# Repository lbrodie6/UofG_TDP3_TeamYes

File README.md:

# UofG_TDP3_TeamYes
UofG TDP3 repo for KiCAD files and code
# File Structure
- hardware: KiCad files. All PCBs can be done within the Main_Project file
    - mechanical: Mechanical CAD files. Fusion 360 .f3d, STLs and Gcode files for 3D printing are all stored here
    - photomasks: Photomasks for PCB fabrication output
- lib: Footprint libraries. Contains any custom footprints used (such as for the FRDM board).
- software: Contains C++ code

## Reference
- TCS34725 Color Sensor design files: https://github.com/adafruit/Adafruit-Flora-TCS34725-Color-Sensor-PCB/tree/master -- could be used for footprint reference
- TCS3472 mbed software library: https://os.mbed.com/users/Allar/code/TCS3472_I2C/docs/tip/classTCS3472__I2C.html
- TCS34725 datasheet: https://cdn-shop.adafruit.com/datasheets/TCS34725.pdf

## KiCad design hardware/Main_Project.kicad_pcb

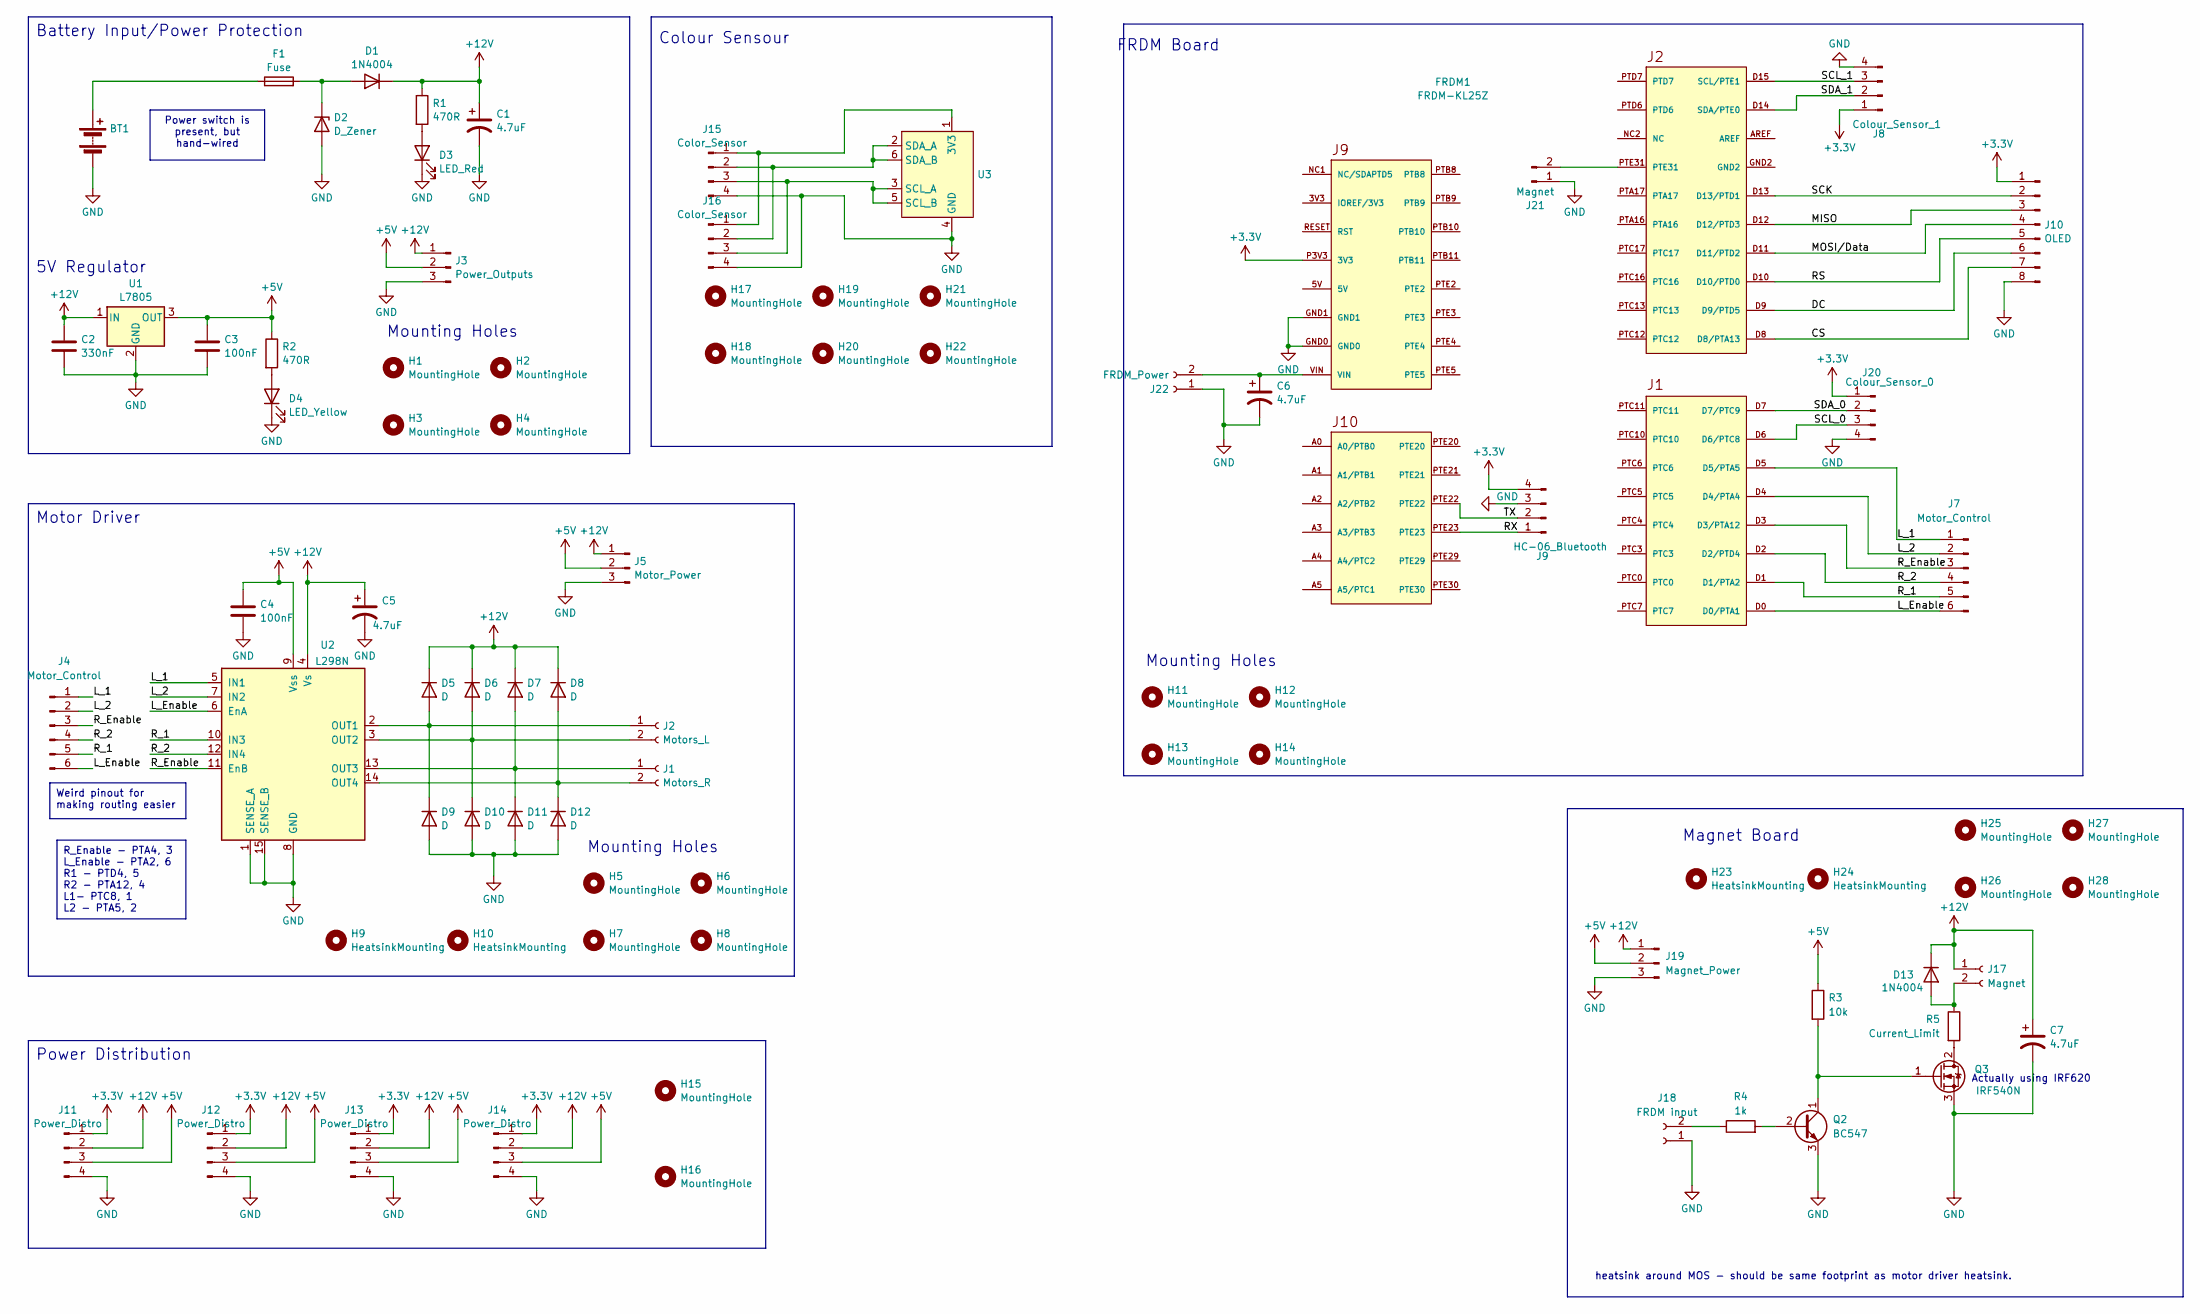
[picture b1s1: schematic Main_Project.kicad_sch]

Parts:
BT1: 12V Battery; TerminalBlock_bornier-2_P5.08mm
C1, C5, C6, C7: 4.7uF; CP_Radial_D8.0mm_P3.50mm
C2: 330nF; C_Disc_D8.0mm_W2.5mm_P5.00mm
C3, C4: 100nF; C_Disc_D8.0mm_W2.5mm_P5.00mm
D1, D13: 1N4004; D_A-405_P10.16mm_Horizontal
D2: D_Zener; D_A-405_P10.16mm_Horizontal
D3: LED_Red; LED_D5.0mm
D4: LED_Yellow; LED_D5.0mm
D5, D6, D7, D8, D9, D10, D11, D12: D; D_A-405_P10.16mm_Horizontal
F1: Fuse; Fuseholder_Cylinder-5x20mm_Schurter_0031_8201_Horizontal_Op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
FRDM1: FRDM-KL25Z; FRDM_KL25Z_NORMAL
H1, H2, H3, H4, H5, H6, H7, H8, H11, H12, H13, H14, H15, H16, H17, H18, H19, H20, H25, H26, H27, H28: MountingHole; MountingHole_3mm
H9, H10, H23, H24: HeatsinkMounting; M3_Heatsink_Mounting
H21, H22: MountingHole; MountingHole_5.3mm_M5
J1: Motors_R; TerminalBlock_bornier-2_P5.08mm
J2: Motors_L; TerminalBlock_bornier-2_P5.08mm
J3: Power_Outputs; TerminalBlock_bornier-3_P5.08mm
J4, J7: Motor_Control; Molex_KK-254_AE-6410-06A_1x06_P2.54mm_Vertical
J5: Motor_Power; TerminalBlock_bornier-3_P5.08mm
J8: Colour_Sensor_1; Molex_KK-254_AE-6410-04A_1x04_P2.54mm_Vertical
J9: HC-06_Bluetooth; Molex_KK-254_AE-6410-04A_1x04_P2.54mm_Vertical
J10: OLED; Molex_KK-254_AE-6410-08A_1x08_P2.54mm_Vertical
J11, J12, J13, J14: Power_Distro; TerminalBlock_bornier-4_P5.08mm
J15, J16: Color_Sensor; Molex_KK-254_AE-6410-04A_1x04_P2.54mm_Vertical
J17: Magnet; TerminalBlock_bornier-2_P5.08mm
J18: FRDM input; Molex_KK-254_AE-6410-02A_1x02_P2.54mm_Vertical
J19: Magnet_Power; TerminalBlock_bornier-3_P5.08mm
J20: Colour_Sensor_0; Molex_KK-254_AE-6410-04A_1x04_P2.54mm_Vertical
J21: Magnet; Molex_KK-254_AE-6410-02A_1x02_P2.54mm_Vertical
J22: FRDM_Power; TerminalBlock_bornier-2_P5.08mm
Q2: BC547; TO-92_Inline_Wide
Q3: IRF540N; TO-220-3_Vertical
R1, R2: 470R; R_Axial_DIN0207_L6.3mm_D2.5mm_P10.16mm_Horizontal
R3: 10k; R_Axial_DIN0207_L6.3mm_D2.5mm_P10.16mm_Horizontal
R4: 1k; R_Axial_DIN0207_L6.3mm_D2.5mm_P10.16mm_Horizontal
R5: Current_Limit; R_Axial_DIN0207_L6.3mm_D2.5mm_P10.16mm_Horizontal
U1: L7805; TO-220-3_Horizontal_TabDown
U2: L298N; TO-220-15_P2.54x2.54mm_StaggerOdd_Lead4.58mm_Vertical
U3: Adafruit_Flora_Sensor

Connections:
+3V3: FRDM1.P3V3 (3V3), J8.1, J9.4, J10.1, J11.1, J12.1, J13.1, J14.1, J20.1
+5V: C3.1, C4.1, J3.2, J5.2, J11.3, J12.3, J13.3, J14.3, J19.2, R2.1, R3.1, U1.3 (OUT), U2.9 (Vss)
+12V: C1.1, C2.1, C5.1, C7.1, D1.1 (K), D5.1 (K), D6.1 (K), D7.1 (K), D8.1 (K), D13.1 (K), J3.1, J5.1, J11.2, J12.2, J13.2, J14.2, J17.1, J19.1, R1.1, U1.1 (IN), U2.4 (Vs)
/CS: FRDM1.D8 (D8/PTA13), J10.7
/DC: FRDM1.D9 (D9/PTD5), J10.6
/L_1: FRDM1.D5 (D5/PTA5), J4.1, J7.1, U2.5 (IN1)
/L_2: FRDM1.D4 (D4/PTA4), J4.2, J7.2, U2.7 (IN2)
/L_Enable: FRDM1.D0 (D0/PTA1), J4.6, J7.6, U2.6 (EnA)
/MISO: FRDM1.D12 (D12/PTD3), J10.3
/MOSI/Data: FRDM1.D11 (D11/PTD2), J10.4
/RS: FRDM1.D10 (D10/PTD0), J10.5
/RX: FRDM1.PTE23, J9.1
/R_1: FRDM1.D1 (D1/PTA2), J4.5, J7.5, U2.10 (IN3)
/R_2: FRDM1.D2 (D2/PTD4), J4.4, J7.4, U2.12 (IN4)
/R_Enable: FRDM1.D3 (D3/PTA12), J4.3, J7.3, U2.11 (EnB)
/SCK: FRDM1.D13 (D13/PTD1), J10.2
/SCL_0: FRDM1.D6 (D6/PTC8), J20.3
/SCL_1: FRDM1.D15 (SCL/PTE1), J8.3
/SDA_0: FRDM1.D7 (D7/PTC9), J20.2
/SDA_1: FRDM1.D14 (SDA/PTE0), J8.2
/TX: FRDM1.PTE22, J9.2
GND: BT1.2 (-), C1.2, C2.2, C3.2, C4.2, C5.2, C6.2, C7.2, D2.2 (A), D3.1 (K), D4.1 (K), D9.2 (A), D10.2 (A), D11.2 (A), D12.2 (A), FRDM1.GND0, FRDM1.GND1, J3.3, J5.3, J8.4, J9.3, J10.8, J11.4, J12.4, J13.4, J14.4, J15.4, J16.4, J18.1, J19.3, J20.4, J21.1, J22.1, Q2.3 (E), Q3.3 (S), U1.2 (GND), U2.1 (SENSE_A), U2.8 (GND), U2.15 (SENSE_B), U3.4 (GND)
unnamed: BT1.1 (+), F1.1
unnamed: D1.2 (A), D2.1 (K), F1.2
unnamed: D3.2 (A), R1.2
unnamed: D4.2 (A), R2.2
unnamed: D5.2 (A), D9.1 (K), J2.1, U2.2 (OUT1)
unnamed: D6.2 (A), D10.1 (K), J2.2, U2.3 (OUT2)
unnamed: D7.2 (A), D11.1 (K), J1.1, U2.13 (OUT3)
unnamed: D8.2 (A), D12.1 (K), J1.2, U2.14 (OUT4)
unnamed: D13.2 (A), J17.2, R5.1
unnamed: J15.1, J16.1, U3.1 (3V3)
unnamed: J15.2, J16.2, U3.2 (SDA_A), U3.6 (SDA_B)
unnamed: J15.3, J16.3, U3.3 (SCL_A), U3.5 (SCL_B)
unnamed: J18.2, R4.1
unnamed: FRDM1.PTE31, J21.2
unnamed: C6.1, FRDM1.VIN, J22.2
unnamed: Q2.2 (B), R4.2
unnamed: Q2.1 (C), Q3.1 (G), R3.2
unnamed: Q3.2 (D), R5.2

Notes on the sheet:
Power switch is present, but hand-wired
Weird pinout for making routing easier
R_Enable - PTA4, 3 L_Enable - PTA2, 6 R1 - PTD4, 5 R2 - PTA12, 4 L1- PTC8, 1 L2 - PTA5, 2
Mounting Holes
Power Distribution
heatsink around MOS - should be same footprint as motor driver heatsink.
5V Regulator
Actually using IRF620
Battery Input/Power Protection
Colour Sensour
FRDM Board
Magnet Board
Motor Driver

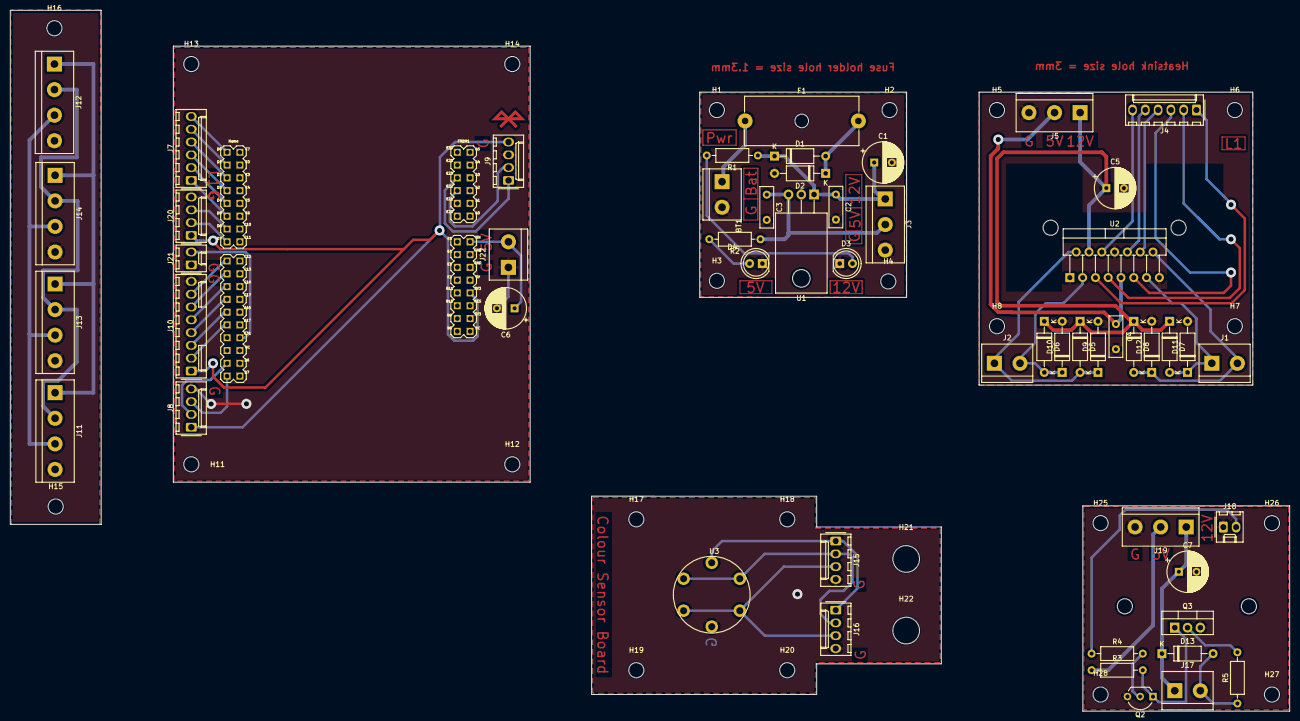
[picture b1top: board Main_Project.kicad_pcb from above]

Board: 2 copper layers, 254.1 x 139.2 mm, 82 parts (0 on the bottom side), 40 nets.

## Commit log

2023-10-13 Added Hardware Files
2023-10-13 kicad backups
2023-10-13 Added example text
2023-10-19 Added footprints for Colour sensor and reorganized libraries
2023-10-23 Changed PCB slightly
2023-10-24 Added colour sensor test code
2023-10-24 Added 'mechanical' for any 3D-printed parts
2023-10-25 Added dual occluder for line sensing
2023-10-25 Colour Sensor Code updated for demo
2023-10-26 Renamed AnalogIn pin
2023-10-26 Create motor(forward and stop)
2023-10-27 Minor changes
2023-10-27 Moved Peter's Motor code
2023-10-27 Created Power PCB
2023-10-27 Created photomasks folder and made photomasks for power PCB
2023-10-27 Separated PDF into top and bottom layers
2023-10-29 Motor Control Code V2
    ZIP file, keil studio
2023-11-01 changed resistor values
2023-11-08 Motor Board
2023-11-08 Revert "Merge branch 'main' of https://github.com/Izaakthegreat/UofG_TDP3_TeamYes"
    This reverts commit c94bb09d7ba82349e4f842fc72250d60d35b9314, reversing
    changes made to e7193e99aa60d7a7ac14a2fac5b26370316d7b60.
2024-01-11 notes for magnet circuit
2024-01-15 Create ColourSensorTestRatios
2024-01-15 Rename ColourSensorTestRatios to ColourSensorTestRatios.cpp
2024-01-15 Colour Sensor board added and adjusted
2024-01-17 added notes for priority of tasks
    xxx
2024-01-17 notes update
2024-01-17 get rid of question marks
2024-01-17 deleted
2024-01-17 Updated Colour Sensor Board to fit properly
2024-01-19 Rename colour_sensor_ranges.txt to colour_sensor_ranges.md
2024-01-21 Colour Sensor Testing with Line Detection updated
    Still need to figure out how data from both sensors will come into the microcontroller
2024-01-22 new pcb for magnet
2024-01-22 Magnet board
2024-01-31 New FRDM Board
2024-02-02 Updated PCB with connections all B-side, and unrouted track fixed
2024-02-02 PCB updated again, one more issue fixed
2024-02-08 Updated FRDM pcb and photomasks
2024-02-08 Updated Sensor code
2024-02-12 kicad autosave bs
2024-02-12 More COlour stuff
2024-02-21 No real changes just weird bits and bobs from opening the kicad I think
2024-02-21 Create main
    Louise 0.1 attempt
2024-02-21 Updated Schematic with correct Pin assignments in notes for Motor Board :)
2024-02-23 blah blah user changes whatever
2024-03-14 Create Louise_FinalLineFollowing
    Line sensors 1,2,3 enabled
2024-03-18 Create colour_sensing_and_movement
2024-03-18 Rename colour_sensing_and_movement to colour_sensing_and_movement.cpp
2024-03-18 Create Louiselinefollow
2024-03-19 Create louisetest1
